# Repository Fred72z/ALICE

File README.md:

# EXTENSION MULTIPORTS ALICE #

Cette extension permet d'étendre les possibilités des ordinateurs MATRA ALICE (4K, 32 et 90).
Elle ajoute :
 - 2 Ports joystick DB9
 - 16K de RAM
 - 2 ports d'extension à l'arrière identiques à celui de l'ALICE
 - un port cartouche sur le dessus.

Elle est aussi compatible avec le MATRA MC10 (identique à l'ALICE 4K).

Ce projet a été réalisé conjointement avec 6502man pour la partie software.

 Ports joystick :\
 Les ports joystick sont compatibles avec l'extension joystick commercialisée à l'époque.
 Ils occupent les adresses $BF30 (48944) pour le joystick droit et $BF34 (48948) pour le joystick gauche.
 
 RAM :\
 La RAM de 16Ko occupe les adresses [$5000-8FFF]. Elle peut être désactivée par un micro interrupteur accessible à l'arriére du boîtier. Une version modifiée du programme du PLD permet d'étendre cette RAM à 24K [$5000-AFFF] permettant de transformer un ALICE 32 en ALICE 90. Toutefois cette modification rend l'extension incompatible avec le 4K.
 
 Ports d'extension :\
 Le boîtier dispose de 2 ports d'extension à l'arrière permettant de régler le gros problème de l'ALICE qui ne permet de connecteur qu'une seule extension à la fois.
 Les 2 ports sont identiques à celui de l'ALICE. Les signaux SEL sont connectés via des diodes afin de permettre l'utilisation de plusieurs extensions simultanément.
 
 Port cartouche :\
 Un port cartouche est placé sur le dessus du boîtier. Il permet d'ajouter des cartouches de jeux ou de langage.
 Ces cartouches disposent d'une mémoire de 64Ko répartie en 8x8Ko ou 4x16Ko selon l'utilisation.

 Mode cartouche :\
 Dans ce mode, la cartouche est vue dans la zone [$1000-2FFF] soit 8Ko. Il est possible de choisir la mémoire parmi 8 blocs (8x8Ko). Le choix du bloc se fait par une écriture dans la zone [$1000-1FFF].
 Le bloc '0' est automatiquement sélectionné à la mise sous tension.
 
 Mode ROM :\
 Dans ce mode, la cartouche est vue dans la zone [$C000-FFFF] soit 16Ko. Il est possible de choisir la mémoire parmi 4 blocs (4x16Ko). Le choix du bloc se fait par une écriture dans la zone [$C000-CFFF].
 Le bloc '0' est automatiquement sélectionné à la mise sous tension.

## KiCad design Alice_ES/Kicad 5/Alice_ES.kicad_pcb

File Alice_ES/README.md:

#EXTENSION 24 ENTREES SORTIES ALICE

Cette extension permet d'ajouter 24 entrées-sorties aux ordinateurs MATRA ALICE (4K, 32 et 90).
Les 24 E/S sont réparties en 3 ports de 8 bits.

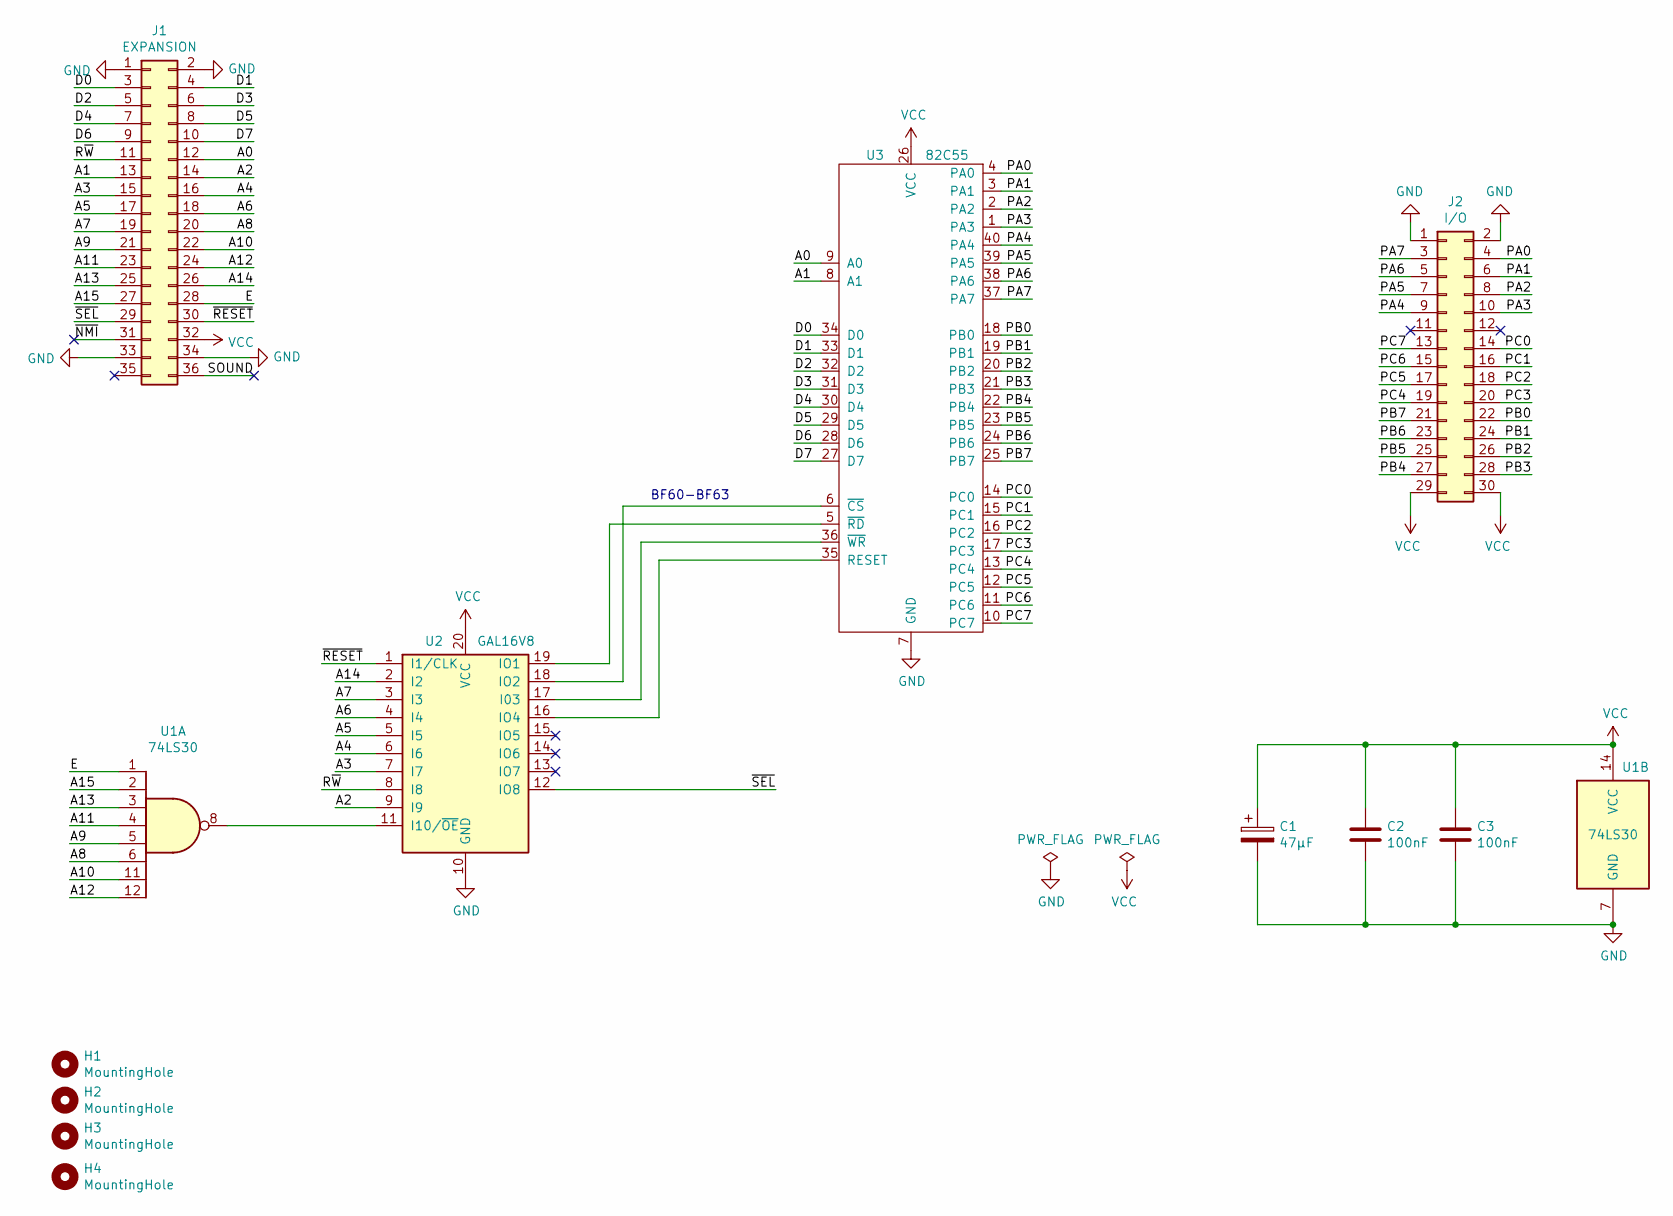
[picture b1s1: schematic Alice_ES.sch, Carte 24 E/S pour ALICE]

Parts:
C1: 47µF; CP_Radial_D5.0mm_P2.54mm_Horizontal
C2, C3: 100nF; C_Ceramic_D5.5mm_W4mm_P5.00mm
H1, H2, H3, H4: MountingHole; MountingHole_3.2mm_M3_DIN965_Pad
J1: EXPANSION; ALICE32
J2: I/O; IDC-Header_2x15_P2.54mm_Horizontal
U1: 74LS30; DIP-14_W7.62mm_LongPads
U2: GAL16V8; DIP-20_W7.62mm_LongPads
U3: 82C55; DIP-40_W15.24mm_LongPads

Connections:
/A0: J1.12, U3.9 (A0)
/A1: J1.13, U3.8 (A1)
/A2: J1.14, U2.9 (I9)
/A3: J1.15, U2.7 (I7)
/A4: J1.16, U2.6 (I6)
/A5: J1.17, U2.5 (I5)
/A6: J1.18, U2.4 (I4)
/A7: J1.19, U2.3 (I3)
/A8: J1.20, U1.6
/A9: J1.21, U1.5
/A10: J1.22, U1.11
/A11: J1.23, U1.4
/A12: J1.24, U1.12
/A13: J1.25, U1.3
/A14: J1.26, U2.2 (I2)
/A15: J1.27, U1.2
/D0: J1.3, U3.34 (D0)
/D1: J1.4, U3.33 (D1)
/D2: J1.5, U3.32 (D2)
/D3: J1.6, U3.31 (D3)
/D4: J1.7, U3.30 (D4)
/D5: J1.8, U3.29 (D5)
/D6: J1.9, U3.28 (D6)
/D7: J1.10, U3.27 (D7)
/E: J1.28, U1.1
/PA0: J2.4, U3.4 (PA0)
/PA1: J2.6, U3.3 (PA1)
/PA2: J2.8, U3.2 (PA2)
/PA3: J2.10, U3.1 (PA3)
/PA4: J2.9, U3.40 (PA4)
/PA5: J2.7, U3.39 (PA5)
/PA6: J2.5, U3.38 (PA6)
/PA7: J2.3, U3.37 (PA7)
/PB0: J2.22, U3.18 (PB0)
/PB1: J2.24, U3.19 (PB1)
/PB2: J2.26, U3.20 (PB2)
/PB3: J2.28, U3.21 (PB3)
/PB4: J2.27, U3.22 (PB4)
/PB5: J2.25, U3.23 (PB5)
/PB6: J2.23, U3.24 (PB6)
/PB7: J2.21, U3.25 (PB7)
/PC0: J2.14, U3.14 (PC0)
/PC1: J2.16, U3.15 (PC1)
/PC2: J2.18, U3.16 (PC2)
/PC3: J2.20, U3.17 (PC3)
/PC4: J2.19, U3.13 (PC4)
/PC5: J2.17, U3.12 (PC5)
/PC6: J2.15, U3.11 (PC6)
/PC7: J2.13, U3.10 (PC7)
/R~W: J1.11, U2.8 (I8)
/SOUND: J1.36
/~NMI: J1.31
/~RESET: J1.30, U2.1 (I1/CLK)
/~SEL: J1.29, U2.12 (IO8)
GND: C1.2, C2.2, C3.2, J1.1, J1.2, J1.33, J1.34, J2.1, J2.2, U1.7 (GND), U2.10 (GND), U3.7 (GND)
unnamed: U1.8, U2.11 (I10/~OE~)
unnamed: U2.16 (IO4), U3.35 (RESET)
unnamed: U2.17 (I03), U3.36 (~WR)
unnamed: U2.18 (IO2), U3.6 (~CS)
unnamed: U2.19 (IO1), U3.5 (~RD)
VCC: C1.1, C2.1, C3.1, J1.32, J2.29, J2.30, U1.14 (VCC), U2.20 (VCC), U3.26 (VCC)

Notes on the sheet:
BF60-BF63

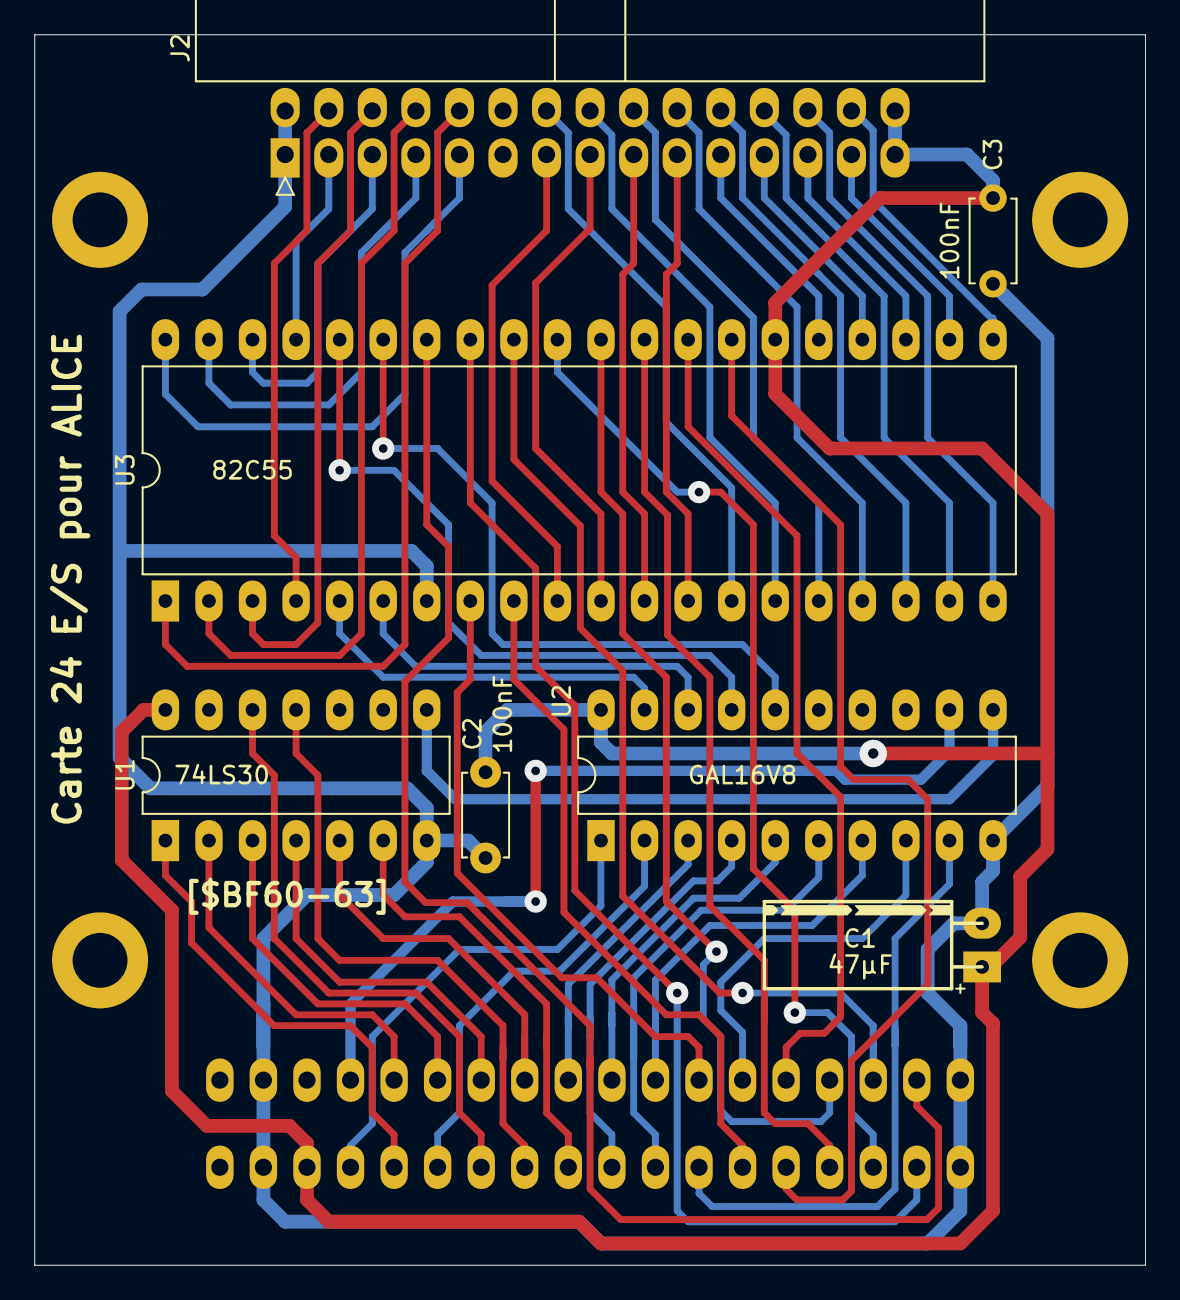
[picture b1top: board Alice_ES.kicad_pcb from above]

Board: 2 copper layers, 64.8 x 71.8 mm, 12 parts (1 on the bottom side), 59 nets.
